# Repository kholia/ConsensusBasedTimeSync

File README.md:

### What?

We present a portable, efficient, passive, consensus based (relative) time
synchronization mechanism over radio waves.

We demonstrate the portability of this mechanism on a bunch of common computing
platforms:

- AMD64 PCs

- Raspberry Pi(s)

- Android phones

- Raspberry Pi Pico (Yep!)

### Why?

FT8, WSPR, and other digital modes need the receivers and the transmitters to
be synchronized in time.

What if there is no external and reliable reference available for time
synchronization?

- RTC clocks can drift over time.

- GPS system can be jammed.

  In comparison, a passive receiver system (i.e. our system) operating over a
  wide range of amateur radio frequencies may be a bit harder to jam.

- Internet may NOT be available in remote areas.

- Sundials can be cumbersome to deploy, calibrate, and perhaps not accurate
  enough ;)

Problem Statement: How do we ensure that we are still able to communicate over
amateur bands using time-synchronized digital modes in absence of external and
reliable references of time?

### How?

Initially, we don't know the (relative) time. We try to decode FT8 traffic with
a timing `fudge factor` of 0. If we don't succeed to decode any traffic, this
`fudge factor` is incremented. This process is repeated until we are able to
decode FT8 traffic successfully. The final value of the `fudge factor` gives
us the (relative) time offset we need.

### Hardware

We use Si4732-A10 IC for HF SSB reception. The Si5351 module provides a clock
output to this Si4732-A10 IC. The other outputs of the Si5351 module can be
used to implement a transmitter.

Thus the whole system is actually a low cost, portable, and efficient digital
transceiver!

The whole system is beginner friendly, and can be built easily on a breadboard
in under an hour or so.

The Si4732-A10 IC is fairly easy to solder on a SMD-To-DIP adapter PCB - no
need to worry about it ;)

For a low-cost alternate option to Si4732-A10, checkout the `CD2003` option
included in this repository.

Tip: Use KiCad 7.x for handling these designs.

Update (September 2023): After on-air testing, we recommend building the
`CD2003-BoB-v2` design included in this repository over other designs for HF!
The `CD2003-S-BoB` design works too but BFO frequency tuning seems like a hard,
finicky process.

Update 2 (November 2023): Please use the `CD2003-BoB-Final` version. It has
some minor correctness fixes in it.

Update 3 (March 2024): Please use the `CD2003-BoB-Final-v2` version. It can be
automatically assembled by JLCPCB!

### Pinout

ATTENTION: The Si4732 IC uses 3.3v signaling! Don't attach it to a 5v MCU
without a bi-directional level shifter.

For sample programs, see https://github.com/pu2clr/SI4735/tree/master/examples.

We include a fully-functional FT8 receiver firmware (for Raspberry Pi Pico) in
this repository. It works on 20m (14.074 MHz) by default. To use this firmware,
write `firmware/run_ft8.uf2` to a Raspberry Pi Pico board.

```
#define CAL            15 // Automatic calibration entry
#define SDA_PIN        12 // GP12 on Pico
#define SCL_PIN        13 // GP13 on Pico
#define RESET_PIN      10 // GP10, Si4732 stuff
```

Si5351 module's CLK 0 goes to `RX_OSC` of Si4732. This has the 32.768 kHz clock
on it.

Si5351 module's CLK 2 goes to GP15 (CAL) of Pico. This is used for automatic
calibration of Si5351 module.

Audio output comes from `L` and `R` pins of the Si4732 BoB.

### Action!

### Credits

https://en.wikipedia.org/wiki/Standing_on_the_shoulders_of_giants

- https://github.com/kgoba/ft8_lib - We use this for FT8 decoding

- https://github.com/aa1gd/pico_ft8_xcvr - Godwin demonstrated ft8_lib powered
  FT8 decoding on Pico first!

- Bradshaw Lupton - For suggesting the original idea and pushing me to do it!

### Prior Work

JTSync and JS8Call are capable of doing time synchronization but they are NOT
portable enough and can't run on microcontrollers!

### Future

We are also interested in automatic, microcontroller based (full) time synchronization systems powered by [WWV](https://www.nist.gov/time-distribution/radio-station-wwv/wwv-and-wwvh-digital-time-code-and-broadcast-format) and other time sources.

And of course, we will be using `DT` values from the decoded FT8 traffic to derive a more accurate `fudge factor` soon!

### References

- https://github.com/kholia/wsprd
- https://en.wikipedia.org/wiki/CHU_(radio_station)
- https://en.wikipedia.org/wiki/WWV_(radio_station)
- https://github.com/kgoba/ft8_lib/
- https://github.com/kholia/pico_ft8_xcvr
- https://github.com/aa1gd/pico_ft8_xcvr

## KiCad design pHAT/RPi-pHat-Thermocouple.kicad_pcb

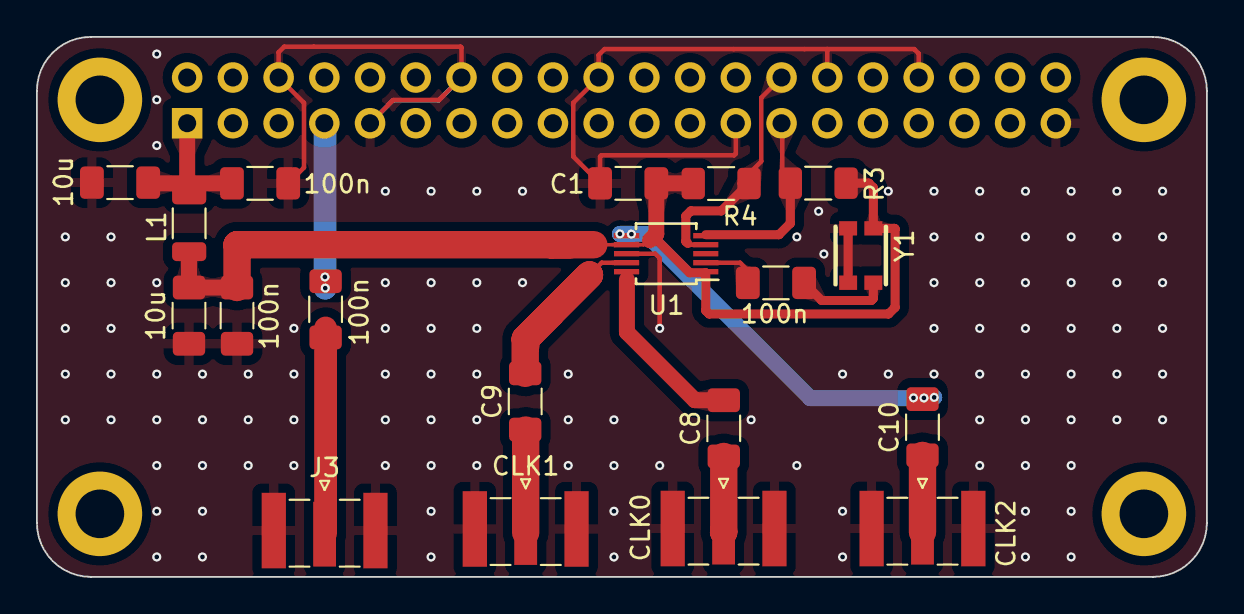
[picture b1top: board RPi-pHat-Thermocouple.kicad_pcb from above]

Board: 2 copper layers, 65.0 x 30.0 mm, 24 parts (1 on the bottom side), 15 nets.

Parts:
C1, C2, C3, C4, C7, C8, C9, C10: 100n; C_1206_3216Metric_Pad1.33x1.80mm_HandSolder
C5, C6: 10u; C_1206_3216Metric_Pad1.33x1.80mm_HandSolder
CLK0, CLK1, CLK2: SMA; SMA_Samtec_SMA-J-P-X-ST-EM1_EdgeMount
H1, H2, H3, H4: MountingHole_Pad; MountingHole_2.7mm_M2.5_DIN965_Pad
J1: RPi_GPIO; PinSocket_2x20_P2.54mm_Vertical_Modded
J3: SMA; SMA_Samtec_SMA-J-P-X-ST-EM1_EdgeMount
L1: 100uH; L_1206_3216Metric
R3, R4: 4.7k; R_1206_3216Metric_Pad1.30x1.75mm_HandSolder
U1: SI5351A; MSOP-10_3x3mm_P0.5mm
Y1: OSCILLATOR; OSC-SMD_4P-L3.2-W2.5-BL_1XTV

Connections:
+3.3V: C1.1, C5.1, C7.1, L1.2, R3.2, R4.2, U1.1 (VDD), U1.7 (VDDO), Y1.4 (VDD)
+3.3VA: C4.2, C6.2, J1.1 (3.3V), L1.1
CLK0: C8.2, U1.10 (CLK0)
CLK1: C9.2, U1.9 (CLK1)
CLK2: C10.2, U1.6 (CLK2)
GND: C1.2, C4.1, C5.2, C6.1, C7.2, CLK0.2 (Ext), CLK1.2 (Ext), CLK2.2 (Ext), J1.6 (GND), J1.9 (GND), J1.14 (GND), J1.20 (GND), J1.25 (GND), J1.30 (GND), J1.34 (GND), J1.39 (GND), J3.2 (Ext), U1.8 (GND), Y1.1 (OE), Y1.2 (GND)
unnamed: C8.1, CLK0.1 (In)
unnamed: C9.1, CLK1.1 (In)
unnamed: C10.1, CLK2.1 (In)
unnamed: C3.1, J1.7 (GPIO04_GCLK)
unnamed: C3.2, J3.1 (In)
unnamed: C2.1, U1.2 (XA)
unnamed: C2.2, Y1.3 (OUT)
SCL: J1.28 (ID_SC), R4.1, U1.4 (SCL)
SDA: J1.27 (ID_SD), R3.1, U1.5 (SDA)

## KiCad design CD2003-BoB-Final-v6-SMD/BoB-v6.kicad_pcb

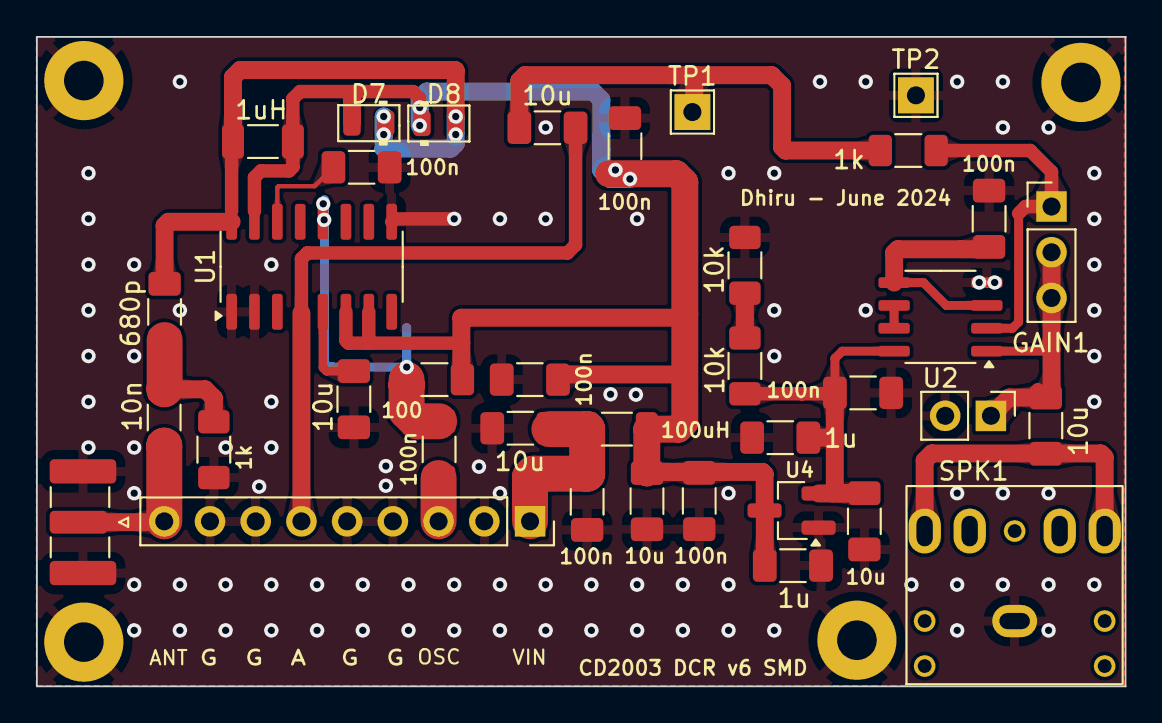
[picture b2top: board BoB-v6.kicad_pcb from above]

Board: 11 copper layers, 60.5 x 36.1 mm, 41 parts (0 on the bottom side), 19 nets.

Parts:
C1, C3, C6, C13, C14, C16: 10u; C_1206_3216Metric_Pad1.33x1.80mm_HandSolder
C2, C4, C5, C8, C9, C10, C12, C21: 100n; C_1206_3216Metric_Pad1.33x1.80mm_HandSolder
C11: 680p; C_1206_3216Metric_Pad1.33x1.80mm_HandSolder
C17: 10n; C_1206_3216Metric_Pad1.33x1.80mm_HandSolder
C18, C19: 1u; C_1206_3216Metric_Pad1.33x1.80mm_HandSolder
D7, D8: CD4148WS; D_0805_2012Metric
GAIN1: 100k; PinHeader_1x03_P2.54mm_Vertical
H1, H2, H3, H4: MountingHole_Pad; MountingHole_2.2mm_M2_Pad
J1: SMA Edge Mount; SMA_Samtec_SMA-J-P-H-ST-EM1_EdgeMount
J2: Conn_01x02; PinHeader_1x02_P2.54mm_Vertical
JP1: Pin Header; PinSocket_1x09_P2.54mm_Vertical_Custom
L1: 1uH; L_1206_3216Metric_Pad1.22x1.90mm_HandSolder
L2: 100uH; L_1206_3216Metric_Pad1.22x1.90mm_HandSolder
R1, R2: 10k; R_1206_3216Metric_Pad1.30x1.75mm_HandSolder
R13: 1k; R_1206_3216Metric_Pad1.30x1.75mm_HandSolder
R14: 100; R_1206_3216Metric_Pad1.30x1.75mm_HandSolder
Rin1: 1k; R_1206_3216Metric_Pad1.30x1.75mm_HandSolder
SPK1: SPEAKER; PJ-307_Modded
TP1: Debug_Audio; TestPoint_THTPad_2.0x2.0mm_Drill1.0mm
TP2: GND; TestPoint_THTPad_2.0x2.0mm_Drill1.0mm
U1: CD2003GB_GP; SOP-16_3.9x9.9mm_P1.27mm
U2: TS922ID; SO-8_3.9x4.9mm_P1.27mm
U4: XC6206P332MR (662K); SOT-23_Handsoldering

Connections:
5VCLEAN: C3.1, C4.1, C8.1, C9.1, C18.1, D7.2 (A), D8.1 (K), L1.2, L2.2, R14.2, U1.6 (VCC), U1.7 (AM_IF), U1.15 (FM_TUNER), U4.3 (VI)
+3.3V: C12.1, C13.1, C19.1, R1.1, U2.8 (V+), U4.2 (VO)
+5V: C5.1, C6.1, JP1.1, L2.1
GND: C2.2, C3.2, C4.2, C5.2, C6.2, C8.2, C9.2, C10.1, C12.2, C13.2, C16.2, C18.2, C19.2, H1.1, H2.1, H3.1, H4.1, J1.2 (Ext), J2.2, JP1.2, JP1.4, JP1.5, JP1.7, JP1.8, R2.2, R13.2, SPK1.S, TP2.1, U1.1 (FM_RF_IN), U1.2 (GND_IN), U1.9 (GND_OUT), U2.4 (V-), U4.1 (GND)
unnamed: C1.2, Rin1.2, TP1.1
unnamed: C11.1, C17.1, R13.1
unnamed: C14.2, SPK1.R, SPK1.T
unnamed: C11.2, D7.1 (K), D8.2 (A), L1.1, U1.16 (AM_RF_IN)
unnamed: C17.2, J1.1 (In), JP1.9
unnamed: C14.1, GAIN1.2, GAIN1.3, J2.1, U2.1
unnamed: R1.2, R2.1
unnamed: C16.1, U1.5 (AGC)
unnamed: C21.1, R14.1, U1.12 (AM_OSC)
unnamed: C10.2, U1.14 (FM/AM_SW)
unnamed: C2.1, U2.3 (+), U2.5 (+)
unnamed: GAIN1.1, Rin1.1, U2.2 (-)
unnamed: U2.6 (-), U2.7
RX_AUDIO: C1.1, JP1.6, U1.4 (AM_MIX)
RX_OSC: C21.2, JP1.3

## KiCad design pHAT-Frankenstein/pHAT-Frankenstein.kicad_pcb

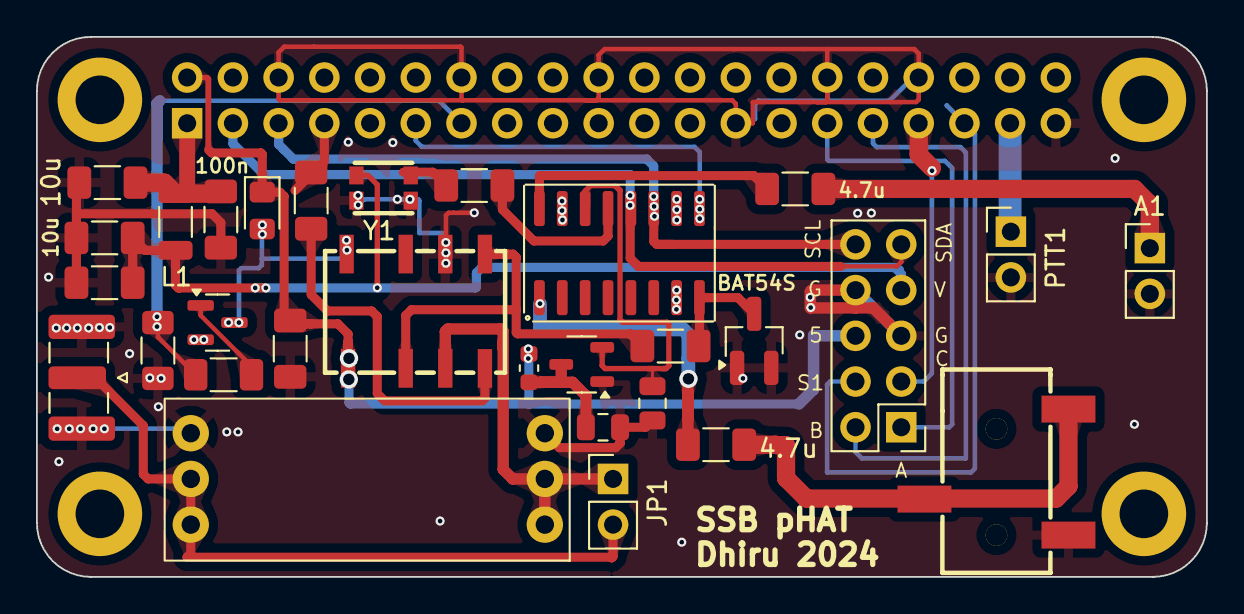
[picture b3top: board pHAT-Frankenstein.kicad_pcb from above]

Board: 2 copper layers, 65.0 x 30.0 mm, 35 parts (1 on the bottom side), 29 nets.

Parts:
A1: Conn_01x02_Pin; PinHeader_1x02_P2.54mm_Vertical
A2: PJ-320B_SMT; AUDIO-SMD_PJ-320B_C2884998_Cut
BPF1: Pluggable SMD BPF (symmetric); Pluggable-BPF
C1, C4, C7, C13: 100n; C_1206_3216Metric_Pad1.33x1.80mm_HandSolder
C2, C8: 1u; C_0805_2012Metric
C3, C12: 4.7u; C_1206_3216Metric_Pad1.33x1.80mm_HandSolder
C5, C6, C10: 10u; C_1206_3216Metric_Pad1.33x1.80mm_HandSolder
C11: 10n; C_1206_3216Metric_Pad1.33x1.80mm_HandSolder
D1: BAT54S; SOT-23_Handsoldering
D2: CD4148WS; D_0805_2012Metric_Pad1.15x1.40mm_HandSolder
ES1: ESC; PinHeader_2x05_P2.54mm_Vertical
H1, H2, H3, H4: MountingHole_Pad; MountingHole_2.7mm_M2.5_DIN965_Pad
J1: RPi_GPIO; PinSocket_2x20_P2.54mm_Vertical_Modded
J3: Conn_Coaxial; SMA_Samtec_SMA-J-P-H-ST-EM1_EdgeMount
JP1: Jumper_2_Open; PinHeader_1x02_P2.54mm_Vertical
K1: HFD4/5-S; RELAY-SMD_HFD4-5-SR
L1: 100uH; L_1206_3216Metric
L2: 100uH; L_0603_1608Metric
PTT1: Conn_01x02_Pin; PinHeader_1x02_P2.54mm_Vertical
Q1: MMBT3904; SOT-23
R1: 10k; R_1206_3216Metric_Pad1.30x1.75mm_HandSolder
R2: 470; R_1206_3216Metric_Pad1.30x1.75mm_HandSolder
U1: XC6206PxxxMR; SOT-23-3
U2: SI4732-A10-GS; SOIC-16_3.9x9.9mm_P1.27mm
Y1: OSCILLATOR; OSC-SMD_4P-L3.2-W2.5-BL_1XTV

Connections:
+3.3V: C5.1, C7.1, ES1.7, L1.2, Y1.4 (VDD)
+3.3VA: C4.2, C6.2, J1.1 (3.3V), L1.1
+5V: C10.1, D2.1 (K), ES1.6, J1.2 (5V), K1.1, L2.1
A: ES1.1, J1.29 (GPIO05)
ANTENNA_IN: BPF1.1 (ANT), BPF1.2 (ANT), JP1.1 (A), K1.3
ANTENNA_OUT: BPF1.4 (RF), BPF1.5 (RF), J3.1 (In), JP1.2 (B)
B: ES1.2, J1.31 (GPIO06)
C: ES1.3, J1.33 (GPIO13)
CLEAN_3.3: C8.1, U1.2 (VO), U2.14 (VDD)
CLK0: C13.2, Y1.3 (OUT)
GND: A1.2, A2.1, BPF1.3 (GND), BPF1.6 (GND), C2.2, C4.1, C5.2, C6.1, C7.2, C8.2, C10.2, D1.1 (A), D1.2 (K), ES1.5, ES1.8, J1.6 (GND), J1.14 (GND), J1.20 (GND), J1.25 (GND), J1.30 (GND), J1.34 (GND), J1.39 (GND), J3.2 (Ext), K1.6, PTT1.2, Q1.2 (E), R1.2, U1.1 (GND), U2.7 (RFGND), U2.10 (SENB), U2.15 (GND), Y1.1 (OE), Y1.2 (GND)
LEFT: A2.2, A2.3, C3.1
unnamed: C11.2, D1.3 (COM), U2.8 (AMI)
unnamed: D2.2 (A), K1.8, Q1.3 (C)
unnamed: C1.1, J1.7 (GPIO04_GCLK)
unnamed: Q1.1 (B), R2.2
unnamed: C2.1, L2.2, U1.3 (VI)
unnamed: C3.2, U2.1 (LOUT/DFS)
unnamed: C13.1, U2.13 (RCLK)
unnamed: C12.1, U2.16 (ROUT/DOUT)
PTT: J1.13 (GPIO27), R1.1, R2.1
PTT_USER: J1.37 (GPIO26), PTT1.1
RF_OUT1: C1.2, K1.4
RIGHT: A1.1, C12.2
RST: J1.11 (GPIO17), U2.9 (*RST)
RX: C11.1, K1.2, K1.5
S1: ES1.4, J1.35 (GPIO19)
SCL: ES1.10, J1.5 (GPIO03_SCL1_I2C), U2.11 (SCLK)
SDA: ES1.9, J1.3 (GPIO02_SDA1_I2C), U2.12 (SDIO)

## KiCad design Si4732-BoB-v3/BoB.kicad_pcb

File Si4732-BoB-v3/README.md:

BAT54S is used for input protection instead of 2x1N4148.

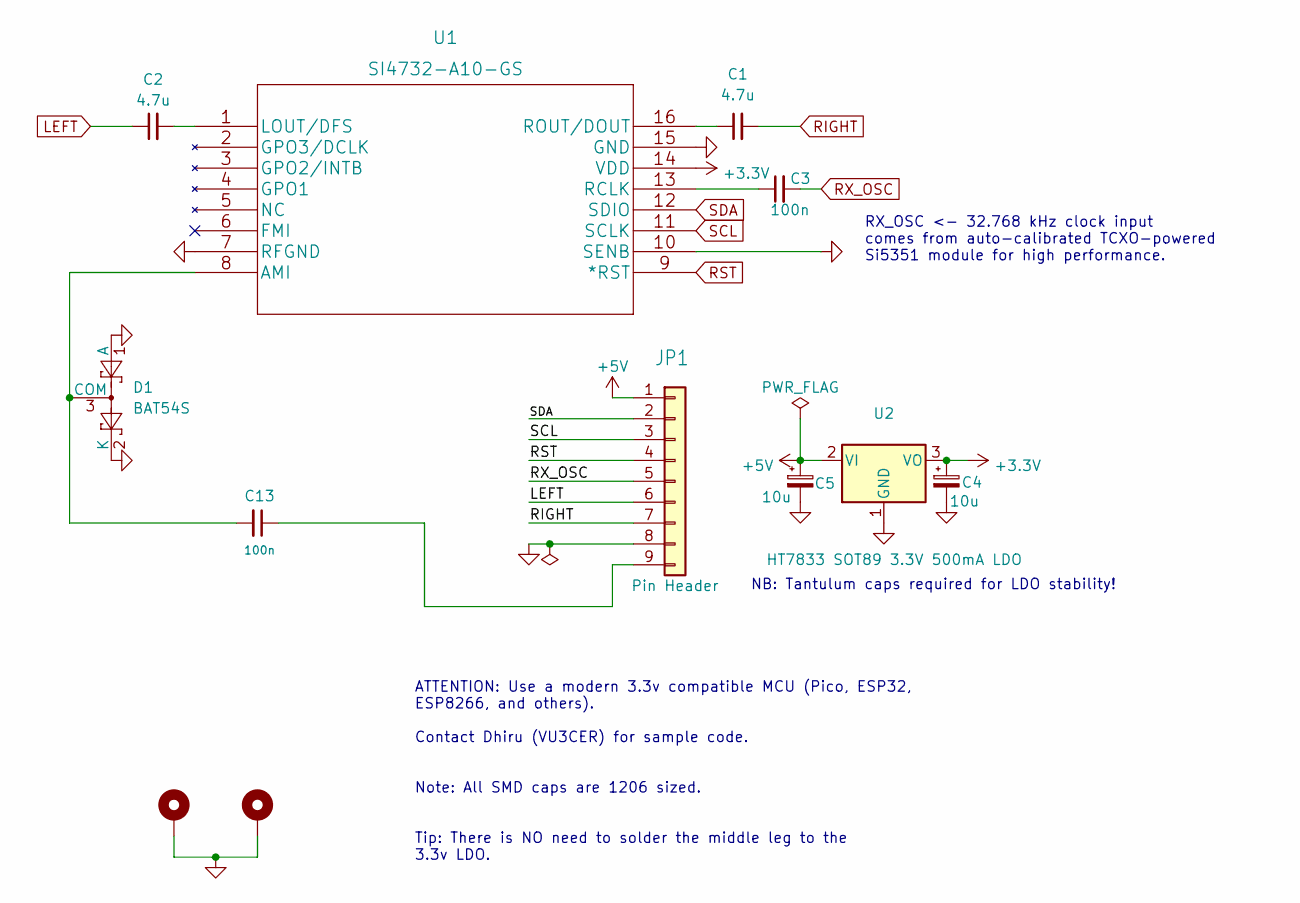
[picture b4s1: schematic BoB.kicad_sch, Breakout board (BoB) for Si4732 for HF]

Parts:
C1, C2: 4.7u; C_1206_3216Metric_Pad1.33x1.80mm_HandSolder
C3, C13: 100n; C_1206_3216Metric_Pad1.33x1.80mm_HandSolder
C4, C5: 10u; CP_EIA-3216-18_Kemet-A_Pad1.58x1.35mm_HandSolder
D1: BAT54S; SOT-23_Handsoldering
H1, H2: MountingHole_Pad; MountingHole_2.2mm_M2_Pad_Via
JP1: Pin Header; PinSocket_1x09_P2.54mm_Vertical_Custom
U1: SI4732-A10-GS; SOIC-16_3.9x9.9mm_P1.27mm
U2: HT7833 SOT89 3.3V 500mA LDO; SOT-89-3_Handsoldering

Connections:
+3.3V: C4.1, U1.14 (VDD), U2.3 (VO)
+5V: C5.1, JP1.1, U2.2 (VI)
GND: C4.2, C5.2, D1.1 (A), D1.2 (K), H1.1, H2.1, JP1.8, U1.7 (RFGND), U1.10 (SENB), U1.15 (GND), U2.1 (GND)
LEFT: C2.1, JP1.6
unnamed: C13.2, D1.3 (COM), U1.8 (AMI)
unnamed: C13.1, JP1.9
unnamed: C2.2, U1.1 (LOUT/DFS)
unnamed: C3.1, U1.13 (RCLK)
unnamed: C1.1, U1.16 (ROUT/DOUT)
RIGHT: C1.2, JP1.7
RST: JP1.4, U1.9 (*RST)
RX_OSC: C3.2, JP1.5
SCL: JP1.3, U1.11 (SCLK)
SDA: JP1.2, U1.12 (SDIO)

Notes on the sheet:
NB: Tantulum caps required for LDO stability!
RX_OSC <- 32.768 kHz clock input comes from auto-calibrated TCXO-powered Si5351 module for high performance.
ATTENTION: Use a modern 3.3v compatible MCU (Pico, ESP32, ESP8266, and others). Contact Dhiru (VU3CER) for sample code. Note: All SMD caps are 1206 sized. Tip: There is NO need to solder the middle leg to the 3.3v LDO.

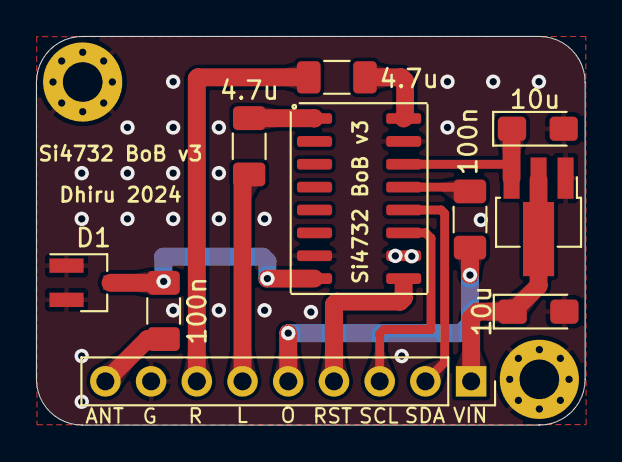
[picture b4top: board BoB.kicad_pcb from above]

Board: 2 copper layers, 30.5 x 21.6 mm, 12 parts (0 on the bottom side), 14 nets.

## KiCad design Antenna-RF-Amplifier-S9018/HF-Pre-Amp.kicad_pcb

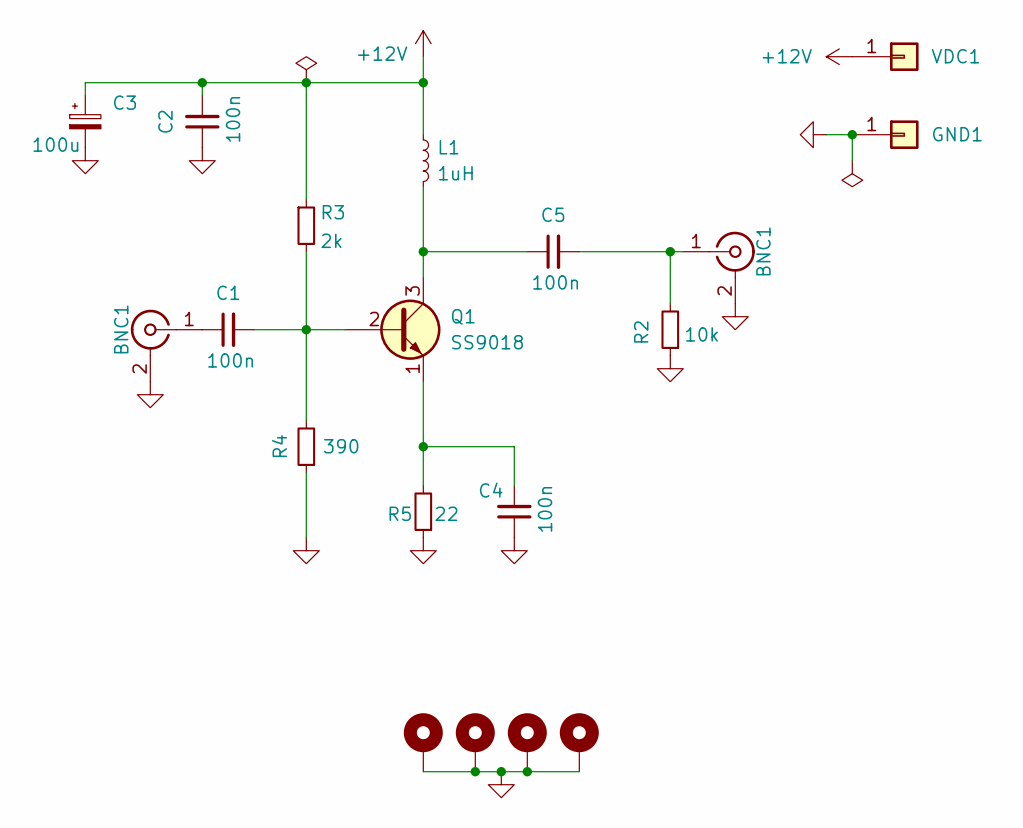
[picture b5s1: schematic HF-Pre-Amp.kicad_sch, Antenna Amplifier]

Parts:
BNC1: SMA; SMA_Samtec_SMA-J-P-H-ST-EM1_EdgeMount
C1, C2, C4, C5: 100n; C_1206_3216Metric_Pad1.33x1.80mm_HandSolder
C3: 100u; CP_Radial_D4.0mm_P2.00mm
GND1: Conn_01x01; TestPoint_THTPad_2.5x2.5mm_Drill1.2mm
H1, H2, H3, H4: MountingHole_Pad; MountingHole_2.2mm_M2_Pad_Via
L1: 1uH; L_Axial_L5.3mm_D2.2mm_P2.54mm_Vertical_Vishay_IM-1
Q1: SS9018; PinSocket_1x03_P2.54mm_Vertical
R2: 10k; R_1206_3216Metric_Pad1.30x1.75mm_HandSolder
R3: 2k; R_1206_3216Metric_Pad1.30x1.75mm_HandSolder
R4: 390; R_1206_3216Metric_Pad1.30x1.75mm_HandSolder
R5: 22; R_1206_3216Metric_Pad1.30x1.75mm_HandSolder
VDC1: Conn_01x01; TestPoint_THTPad_2.5x2.5mm_Drill1.2mm

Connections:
+12V: C2.2, C3.1, L1.1, R3.1, VDC1.1
GND: C2.1, C3.2, C4.1, GND1.1, H1.1, H2.1, H3.1, H4.1, R2.1, R4.1, R5.1; also elsewhere on the board
unnamed 2: C1.1; also elsewhere on the board
unnamed 3: C5.2, R2.2; also elsewhere on the board
unnamed: C1.2, Q1.2 (B), R3.2, R4.2
unnamed: C5.1, L1.2, Q1.3 (C)
unnamed: C4.2, Q1.1 (E), R5.2

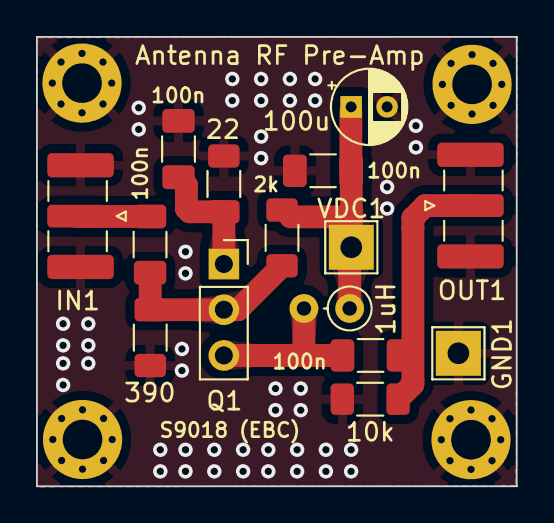
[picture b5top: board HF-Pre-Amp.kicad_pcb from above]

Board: 2 copper layers, 26.7 x 25.0 mm, 19 parts (0 on the bottom side), 7 nets.

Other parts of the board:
IN1: SMA; SMA_Samtec_SMA-J-P-H-ST-EM1_EdgeMount
OUT1: SMA; SMA_Samtec_SMA-J-P-H-ST-EM1_EdgeMount

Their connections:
GND: IN1.2 (Ext), OUT1.2 (Ext); also elsewhere on the board
unnamed 2: IN1.1 (In); also elsewhere on the board
unnamed 3: OUT1.1 (In); also elsewhere on the board

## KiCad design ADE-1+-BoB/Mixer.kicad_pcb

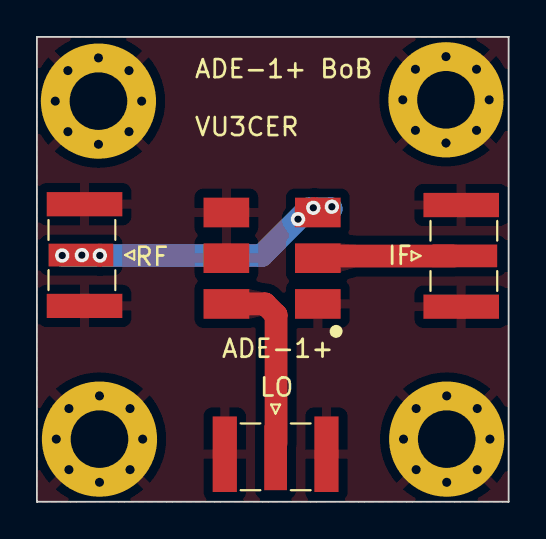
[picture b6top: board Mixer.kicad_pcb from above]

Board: 2 copper layers, 26.2 x 25.8 mm, 8 parts (0 on the bottom side), 4 nets.

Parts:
H1, H2, H3, H4: MountingHole_Pad; MountingHole_3.2mm_M3_Pad_Via
MX1: ADE-1+; CD636_Modded
SMA1: RF; SMA_Samtec_SMA-J-P-X-ST-EM1_EdgeMount
SMA2: LO; SMA_Samtec_SMA-J-P-X-ST-EM1_EdgeMount
SMA3: IF; SMA_Samtec_SMA-J-P-X-ST-EM1_EdgeMount

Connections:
GND: H1.1, H2.1, H3.1, H4.1, MX1.1, MX1.4, MX1.5, SMA1.2 (Ext), SMA2.2 (Ext), SMA3.2 (Ext)
unnamed: MX1.2 (IF), SMA3.1 (In)
unnamed: MX1.6 (LO), SMA2.1 (In)
unnamed: MX1.3 (RF), SMA1.1 (In)

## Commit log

2023-09-23 CD2003 in superhet and DCR modes
2023-09-28 In-flight projects and ideas
2024-03-20 pHAT
